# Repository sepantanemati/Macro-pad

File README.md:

The Macro Pad:

A macro pad is a compact, standalone auxiliary keypad in which each key can be programmed to execute shortcuts, launch applications, or perform multi-step automated commands with a single press.

My primary goal with this macro pad is to enable shortcut activation with a single click.

Components Used:
- Transparent Blue Axis Switch with Puller, 3-Pin Keyboard Switches
- Raspberry Pi Pico
- Keycaps (3D printed)

The PCB is designed using KiCad.

This project is developed for https://halflife.hackclub.com/

schematic:

pcb layout:

3d pcb layout:

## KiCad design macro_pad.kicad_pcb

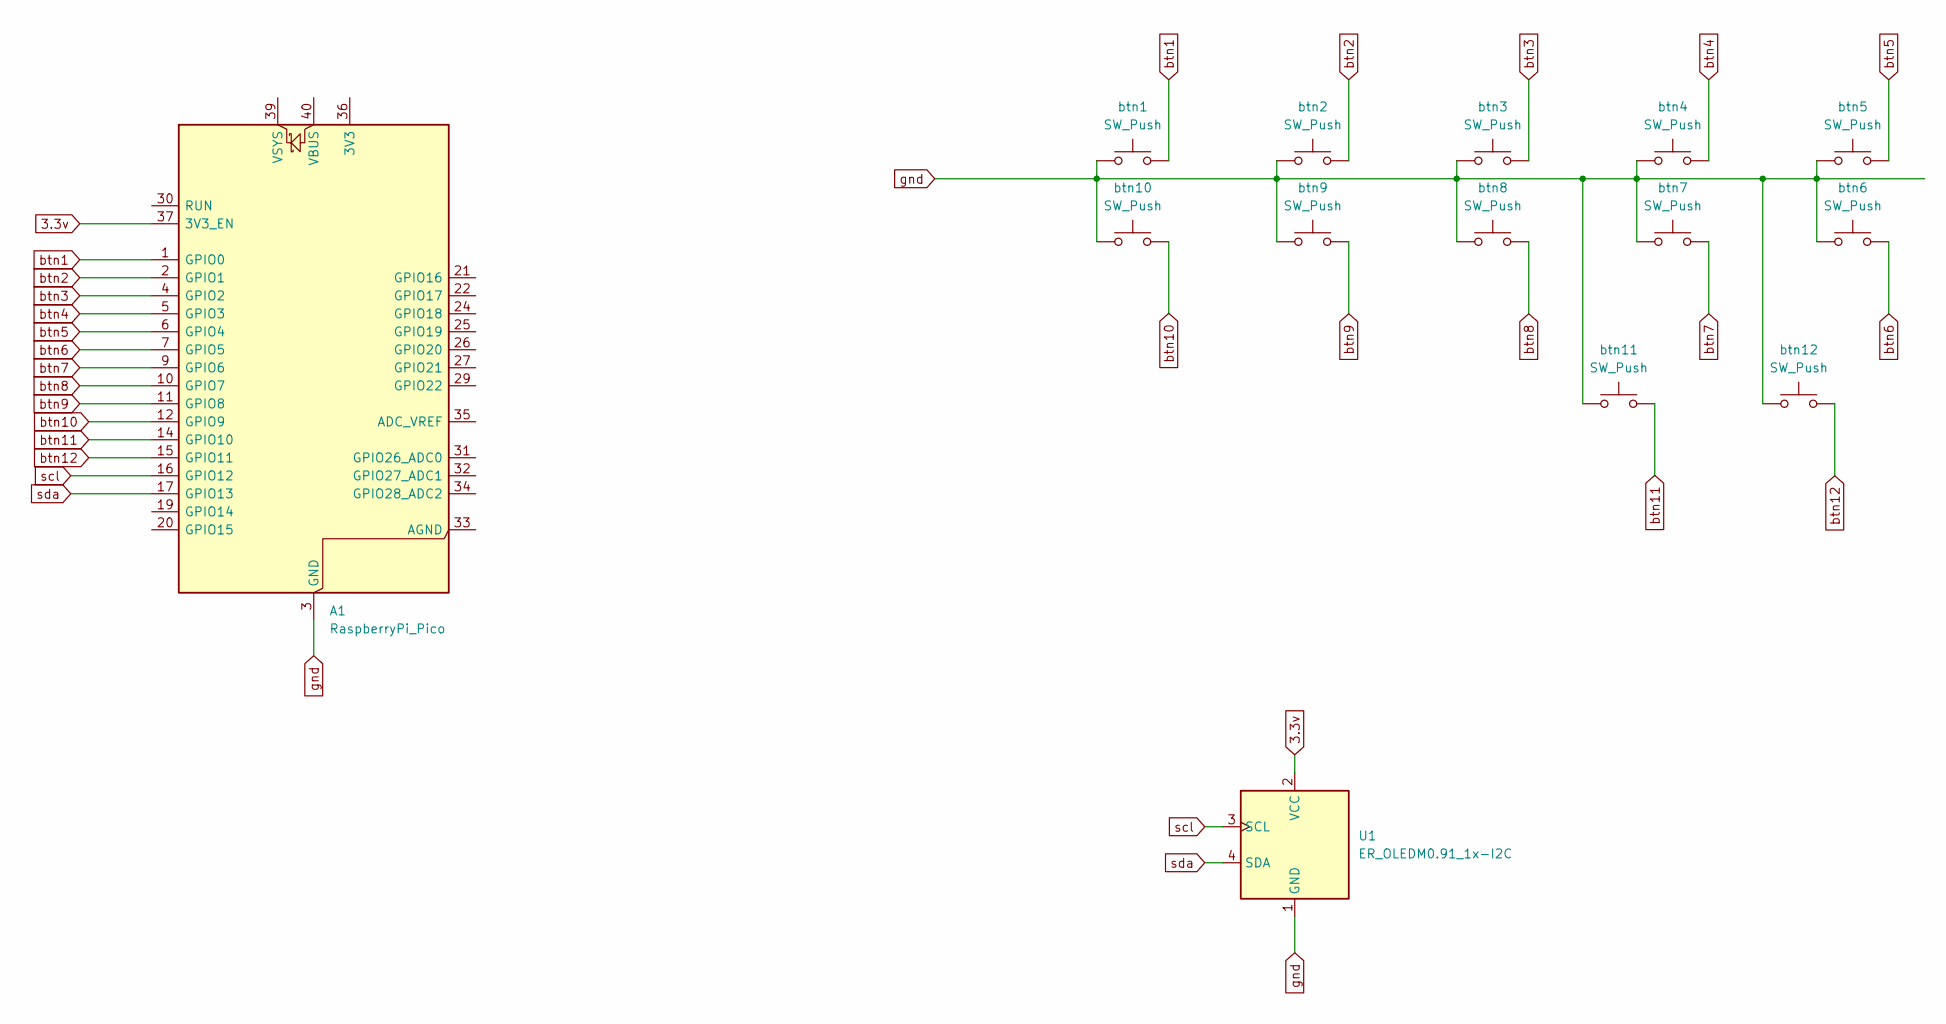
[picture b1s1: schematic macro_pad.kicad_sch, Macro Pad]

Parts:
A1: RaspberryPi_Pico; RaspberryPi_Pico_Common_Unspecified
U1: ER_OLEDM0.91_1x-I2C
btn1, btn2, btn3, btn4, btn5, btn6, btn7, btn8, btn9, btn10, btn11, btn12: SW_Push; SW_Cherry_MX_1.00u_PCB

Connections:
3.3v: A1.37 (3V3_EN), U1.2 (VCC)
btn1: A1.1 (GPIO0), btn1.2
btn2: A1.2 (GPIO1), btn2.2
btn3: A1.4 (GPIO2), btn3.2
btn4: A1.5 (GPIO3), btn4.2
btn5: A1.6 (GPIO4), btn5.2
btn6: A1.7 (GPIO5), btn6.2
btn7: A1.9 (GPIO6), btn7.2
btn8: A1.10 (GPIO7), btn8.2
btn9: A1.11 (GPIO8), btn9.2
btn10: A1.12 (GPIO9), btn10.2
btn11: A1.14 (GPIO10), btn11.2
btn12: A1.15 (GPIO11), btn12.2
gnd: A1.3 (GND), A1.8 (GND), A1.13 (GND), A1.18 (GND), A1.23 (GND), A1.28 (GND), A1.38 (GND), U1.1 (GND), btn1.1, btn2.1, btn3.1, btn4.1, btn5.1, btn6.1, btn7.1, btn8.1, btn9.1, btn10.1, btn11.1, btn12.1
scl: A1.16 (GPIO12), U1.3 (SCL)
sda: A1.17 (GPIO13), U1.4 (SDA)

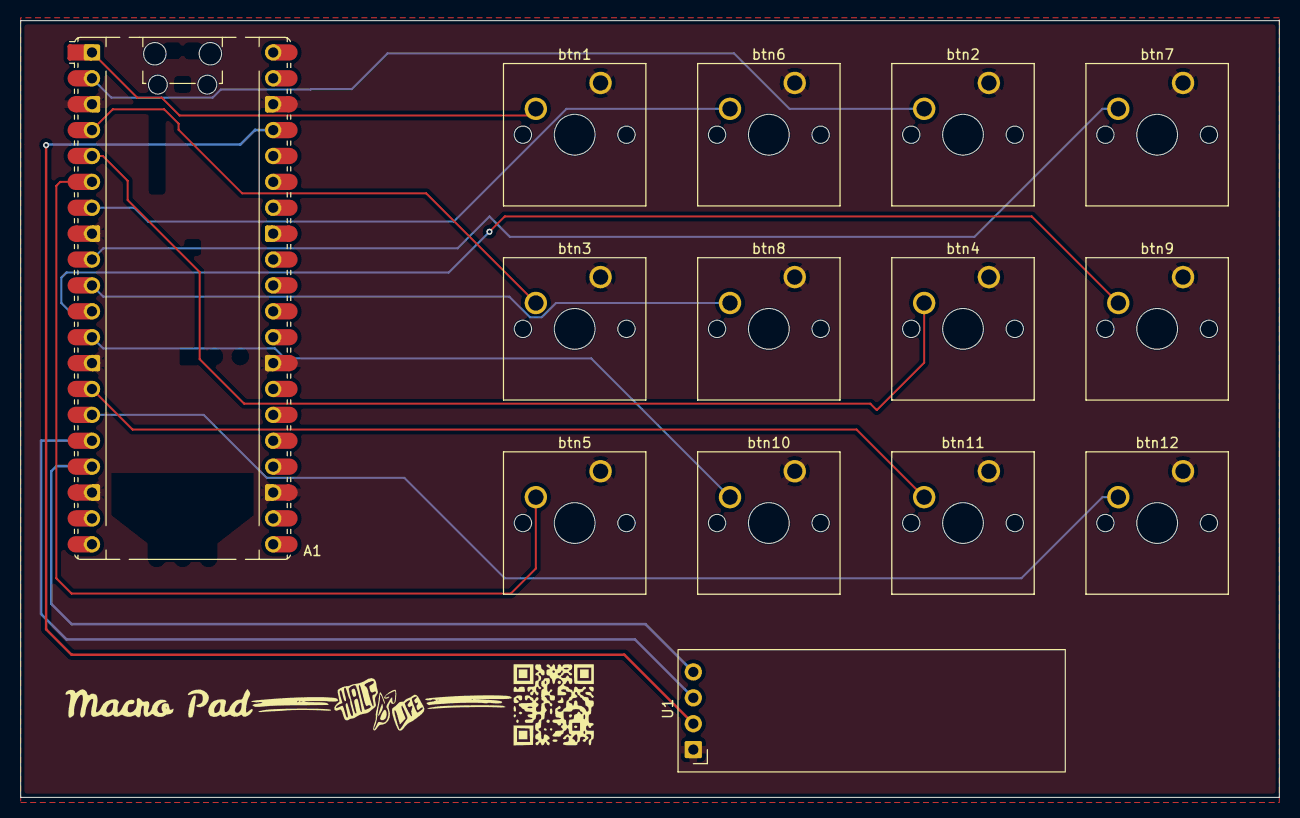
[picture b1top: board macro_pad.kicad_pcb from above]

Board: 2 copper layers, 123.5 x 76.2 mm, 14 parts (0 on the bottom side), 16 nets.
